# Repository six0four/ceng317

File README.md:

# I2C device addresses   
MAG3110 3-Axis Magnetometer (0x0E)   
Si4713 FM Transmitter with RDS (0x11)   
VCNL40x0 proximity sensor (0x13)   
LIS3DH 3-axis accelerometer (0x18)   
LSM303 Accelerometer & Magnetometer (0x19 for accelerometer and *0x1E for magnetometer)   
MCP9808 temp sensor (0x1A)   
MMA845x 3-axis Accelerometer (0x1C)   
LSM9DS0 9-axis IMU (0x1D for Accel/Mag, *0x6A for Gyro)   
*LSM303 Accelerometer & Magnetometer (0x19 for accelerometer and *0x1E for magnetometer)   
FXOS8700 Accelerometer/Magnetometer (0x1F)   
Chirp! Water sensor (0x20)   
FXAS21002 Gyroscope (0x21)   
MCP23008 I2C GPIO expander (0x22)   
MCP23017 I2C GPIO expander (0x23)   
VL53L0x ToF distance (0x24 software selectable)   
BNO055 IMU (0x28)   
TCS34725 color sensor (0x29)   
CAP1188 8-channel Capacitive Touch (0x2A)   
FT6x06 Capacitive Touch Driver (0x38)   
VEML6070 UV Index (0x39)   
SSD1305 monochrome OLED (0x3C)   
SSD1306 monochrome OLED (0x3D)   
HTU21D-F Humidity/Temp Sensor (0x40)   
STMPE610/STMPE811 Resistive Touch controller (0x41)   
HDC1008 Humidity/Temp sensor (0x42)   
ISL29125 Color Sensor (0x44)   
SHT31 Humidity/Temp sensor (0x45)   
TMP006 IR Temperature sensor (0x46)   
TMP007 IR Temperature sensor (0x47)   
YL-40 PCF8591 (0x48)   
TSL2561 light sensor (0x49)   
TMP102 Temperature sensor (0x4A)   
ADS1115 4-channel 16-bit ADC (0x4B)   
INA219 High-Side DC Current/Voltage sensor (0x4C)   
MB85RC I2C FRAM (0x50)   
Nintendo Nunchuck controller (0x52)   
ADXL345 3-axis accelerometer (0x53)   
MAX3010x Pulse & Oximetry sensor (0x57)   
TPA2016 I2C-controlled Amplifier (0x58)   
DRV2605 Haptic Motor Driver (0x5A)   
CCS811 VOC sensor (0x5B)   
AM2315 Humidity/Temp sensor (0x5C)   
MPR121 12-point capacitive touch sensor (0x5D)   
TEA5767 Radio receiver (0x60)   
Si5351A Clock Generator (0x61)   
MCP4725A1 12-bit DAC (0x62)   
MCP4725A2 12-bit DAC (0x64)   
MCP4725A3 12-bit DAC (0x66)   
DS3231 RTC (0x68)   
AMG8833 IR Thermal Camera Breakout (0x69)   
*LSM9DS0 9-axis IMU (0x1D for Accel/Mag, *0x6A for Gyro)   
L3GD20H gyroscope (0x6B)   
TCA9548 1-to-8 I2C Multiplexer (0x70)   
HT16K33 LED Matrix Driver (0x72)   
IS31FL3731 144-LED CharliePlex driver (0x74)   
PCA9685 16-channel PWM driver (0x75)   
MS5607/MS5611 Barometric Pressure (0x76)   
BME280 Temp/Barometric/Humidity (0x77)   
PN532 NFC/RFID reader (Use UART pins 8:TX and 10:RX)

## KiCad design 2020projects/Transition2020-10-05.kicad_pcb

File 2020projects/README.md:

# CENG 317
1. Two device power considerations:
    1. Second STM32 configured as an CAN rear: First is powered via Serial to TTL converter. As long as there is minimal load, joining the 3.3V pins would allow the second to also power from the Serial to TTL converter.
    2. Second STM32 configured as an STLink: Second is powered from USB using its regulator for 3.3V; it would also supply the first weakly over the 3.3V SWD pin.
    3. Second STM32 configured as an I2C slave: First is powered by USB using its regulator for 3.3V; ideally joining the 5V pins allows the second to also use its own regulator but for now as long as there is minimal load, joining the 3.3V pins would allow the second to also use the first's regulator.
2. Electronic part naming conventions:
    1. Resistors start with R followed by a number. R32 is a pull up that has yet to be placed.
	2. Capacitors start with a C followed by a number.
	3. Headers start with a J followed by a number.
	4. 3.3V net label used for CANmain/I2Cmaster/STLinkTarget STM32 (J0,J1).
	5. GND net label used for common connection to CANmain/I2Cmaster/STLinkTarget STM32 (J0,J1) and CANrear/I2Cslave/STLink STM32 (J2,J3). Although some designers use a ground disconnect and open drain design to separate circuits it is problematic when using shielded cables and considering what would happen when a cable gets pinched. We will try to disconnect power instead.
3. J Headers, note that uSD disconnect is simply removing the card:
    0. CANmain/I2Cmaster/STLinkTarget STM32
	1. CANmain/I2Cmaster/STLinkTarget STM32
	2. CANrear/I2Cslave/STLink STM32
	3. CANrear/I2Cslave/STLink STM32
	4. PCF8574, Joystick, 7 Segment disconnect
	5. Servo pin header
	6. Flash disconnect
	7. BME disconnect
	8. Flow control disconnect
	9. Flow control disconnect
	10. Programming port/for serial TTL cable
	11. Inter STM32 3.3V disconnect
	12. STLink voltage divider disconnect
	13. MOSIsd
	14. MISOsd
	15. SCKsd
	16. NSSsd
	17. MOSIflash
	18. MISOflash
	19. SCKflash
	20. NSSflash
	21. MOSIbme
	22. MISObme
	23. SCKbme
	24. NSSbme
	25. PCF8574 Interrupt disconnect
	26. PCF8574 SDA choice
	27. PCF8574 SCL choice
	28. CAN disconnect
	29. CAN disconnect
	30. CAN disconnect
	31. CAN LEDs power disconnect
	32. STLink header
	33. STLink R37 disconnect
	34. STLink NRST disconnect
	35. DS18B20 disconnect
	36. TTL3.3V disconnect
	37. SDAslave disconnect
	38. SCLslave disconnect
	39. LM75-OLED DC
	40. LM75-OLED RST
	41. OLED MOSI
	42. OLED SCK
	43. OLED NSS
	44. OLED 3.3V

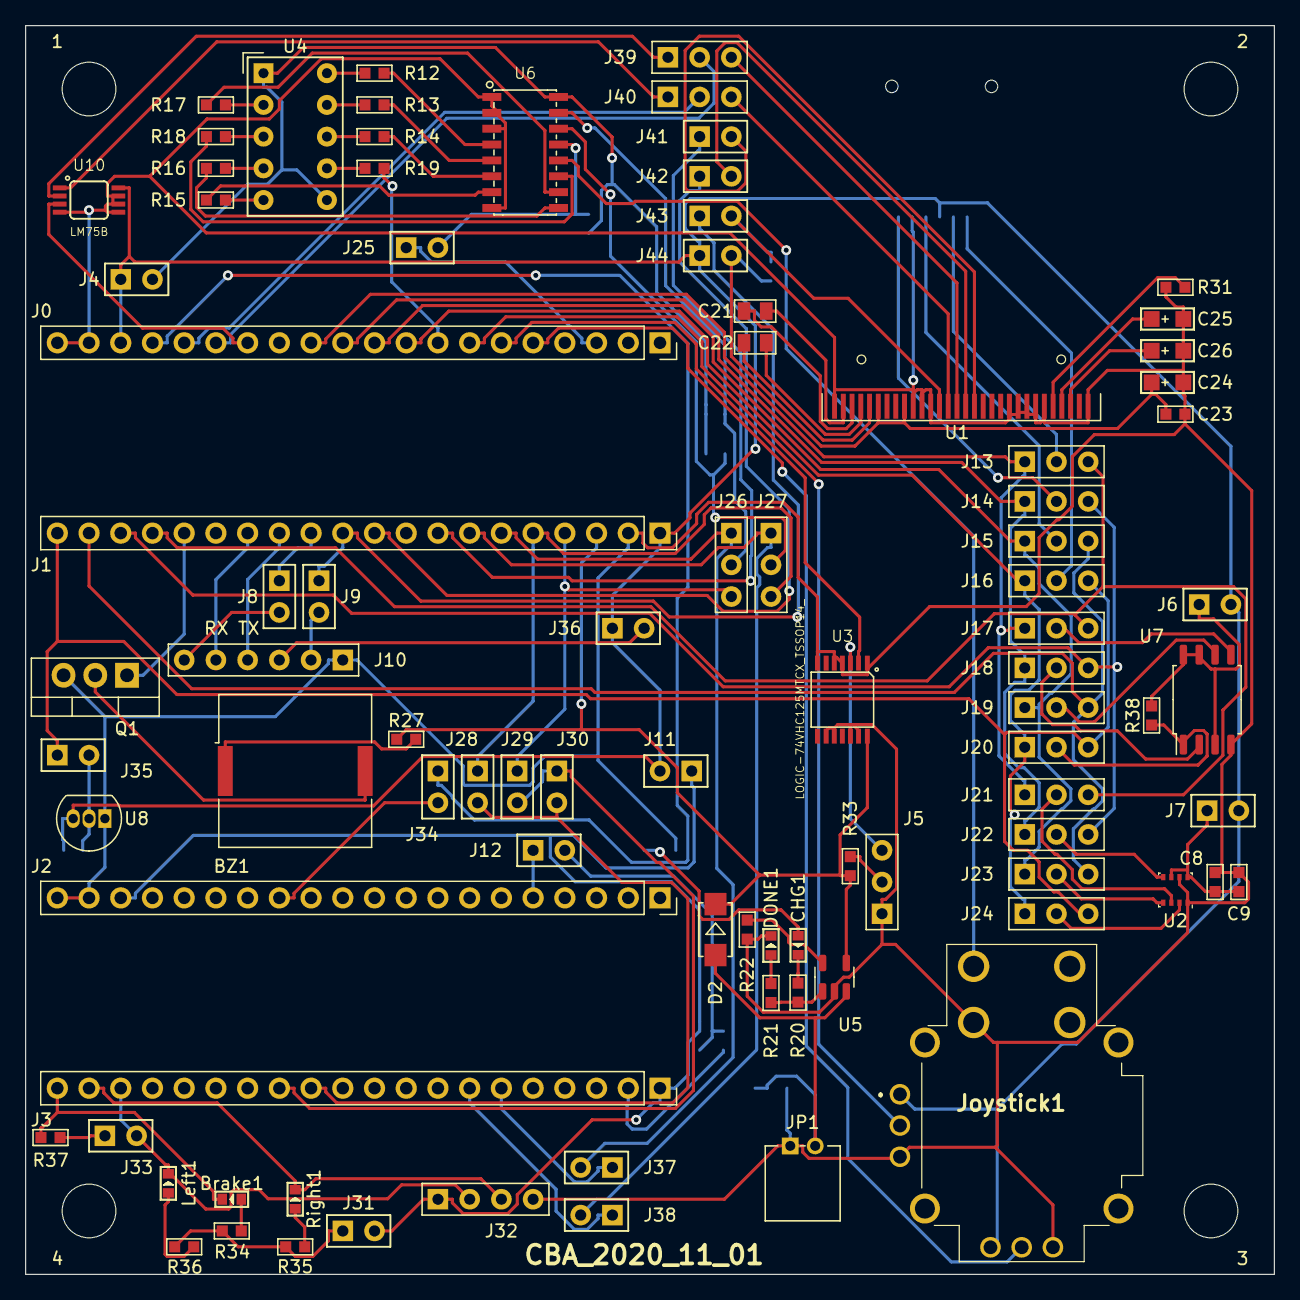
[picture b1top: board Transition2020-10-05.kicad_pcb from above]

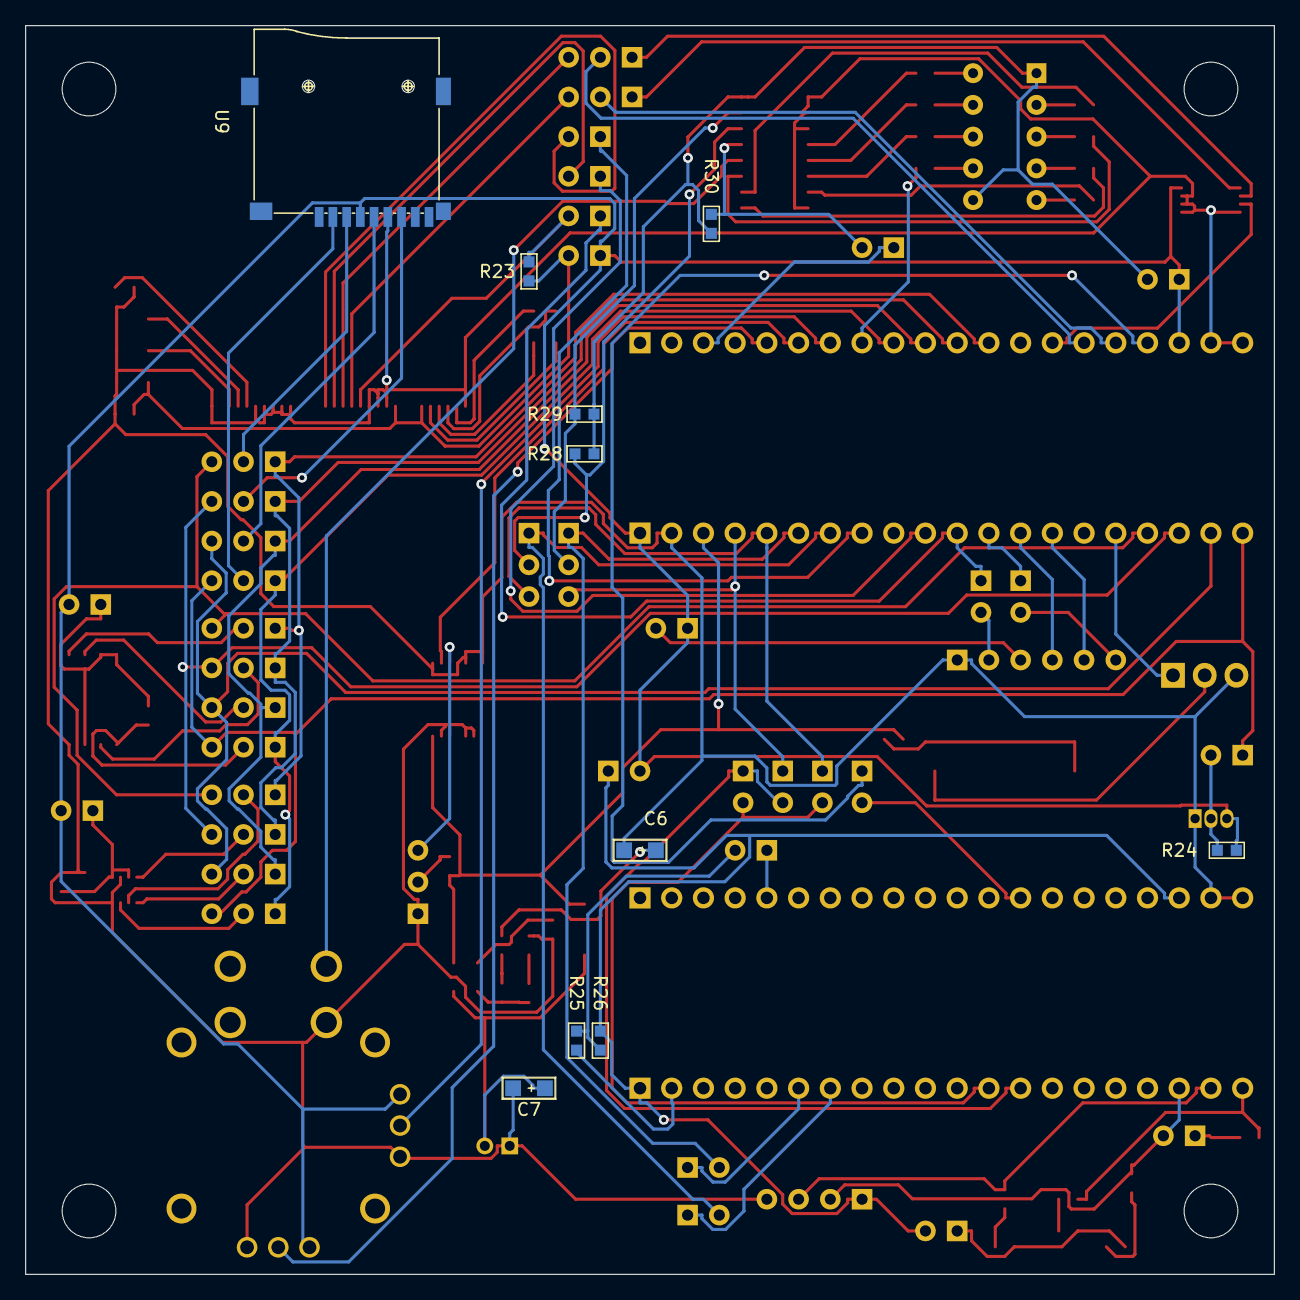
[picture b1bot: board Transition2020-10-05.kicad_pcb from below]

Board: 2 copper layers, 100.0 x 100.0 mm, 105 parts (10 on the bottom side), 111 nets.

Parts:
1, 2, 3, 4: MountingHole_4.3mm_M4_ISO7380
BZ1: Buzzer; Buzzer_Murata_PKLCS1212E
Brake1: LED-SMD-RED-DIFFUSED_0603_; LED-0603
C6, C7, C24, C25, C26: TANTALUM-SMD-10UF-10V-10%_AVX-A_; AVX-A(1206)
C8, C9, C23: CERAMIC-100NF-50V-10%-X7R_0603_; C0603
C21, C22: CERAMIC-2.2UF-25V-10%-X7R_0805_; C0805
CHG1: LED-SMD-RED-DIFFUSED_0603_; LED-0603
D2: SMD-DIODE-SCHOTTKY-40V-1A_DO-214AC_; DO-214AC
DONE1: SMD-LED-CLEAR-GREEN_0603_; LED-0603
J0, J1, J2, J3: Conn_01x20_Female; PinSocket_1x20_P2.54mm_Vertical
J4, J6, J7, J8, J9, J11, J12, J25, J28, J29, J30, J31, J33, J34, J35, J36, J37, J38, J41, J42, J43, J44: DIP-BLACK-MALE-HEADER-VERT_2P-2.54_; H2-2.54
J5, J13, J14, J15, J16, J17, J18, J19, J20, J21, J22, J23, J24, J26, J27, J39, J40: DIP-BLACK-MALE-HEADER-VERT_3P-2.54_; H3-2.54
J10: DIP-BLACK-MALE-HEADER_6P-2.54_; H6-2.54
J32: DIP-BLACK-MALE-HEADER-VERT_4P-2.54_; H4-2.54
JP1: DIP-JST-2P-2.0; H2-2.0-90D
Joystick1: RKJXK122400Y
Left1: SMD-LED-CLEAR-GREEN_0603_; LED-0603
Q1: MJE13005G; TO-220-3_Vertical
R12, R13, R14, R15, R16, R17, R18, R19, R34, R35, R36, R37: SMD-RES-220R-5%-1_10W_0603_; R0603
R20, R21, R27: SMD-RES-1K-5%-1_10W_0603_; R0603
R22, R38: SMD-RES-10K-5%-1_10W_0603_; R0603
R23, R24, R25, R26, R28, R29, R30: SMD-RES-4.7K-5%-1_10W_0603_; R0603
R31: SMD-RES-560K-5%-1_10W_0603_; R0603
R33: SMD-RES-10R-5%-1_10W_0603_; R0603
Right1: SMD-LED-CLEAR-GREEN_0603_; LED-0603
U1: OLED-128O064D
U2: BME280; Bosch_LGA-8_2.5x2.5mm_P0.65mm_ClockwisePinNumbering
U3: LOGIC-74VHC125MTCX_TSSOP14_; TSSOP14-0.65-5X4.4MM
U4: HDSP-7801
U5: MCP73831-2-OT; SOT-23-5
U6: PCF8574; SOP16-1.27-10.0X5.0MM
U7: W25Q32JVSS; SOIC-8_5.23x5.23mm_P1.27mm
U8: DS18B20; TO-92_Inline
U9: MICRO-SD-CARD-HOLDER-9P; MICRO-SD9+4P-SMD-16.1X14.5X1.85MM
U10: LM75B; MSOP8-0.65-3X3MM

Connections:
3.3V: J0.18, J1.1, J4.1, J6.2, J7.2, J11.2, J36.1, J44.1, Joystick1.1, Joystick1.4, R24.1, U8.3, U9.4, U10.8
3.3Vs: J2.18, J3.1, J11.1, J31.2, J32.1, R26.2
5V: D2.2, J1.3, R27.1, R33.1, U3.14, U5.4
GND: C6.2, C7.2, C8.2, C9.2, C23.2, C24.2, C25.2, C26.2, DONE1.2, J0.19, J0.20, J1.2, J2.19, J2.20, J5.1, J10.1, J32.4, JP1.1, Joystick1.3, Joystick1.6, Joystick1.C1, Q1.3, R22.1, R31.1, U1.1, U1.10, U1.11, U1.12, U1.21, U1.22, U1.23, U1.24, U1.25, U1.30, U2.1, U2.7, U3.1, U3.4, U3.5, U3.7, U3.9, U3.10, U3.12, U3.13, U5.2, U6.1, U6.2, U6.3, U6.8, U7.4, U8.1, U9.6, U10.4, U10.5, U10.6, U10.7
GNDs: J3.2, R25.1
MISO1: J0.11, J14.1, J18.1, J22.1
MISO2: J1.18, J14.3, J18.3, J22.3
MISObme: J22.2, U2.5
MISOflash: J18.2, U7.2
MISOsd: J14.2, U9.7
MOSI1: J0.12, J13.1, J17.1, J21.1
MOSI2: J1.17, J13.3, J17.3, J21.3
MOSIbme: J21.2, U2.3
MOSIflash: J17.2, U7.5
MOSIsd: J13.2, U9.3
NRST: J0.17, J34.1
NSS1: J0.9, J16.1, J20.1, J24.1
NSS2: J1.20, J16.3, J20.3, J24.3, J35.1
NSSbme: J24.2, U2.2
NSSflash: J20.2, R38.1, U7.1
NSSsd: J16.2, U9.2
unnamed: BZ1.1, R27.2
unnamed: BZ1.2, Q1.2
unnamed: Brake1.1, R34.2
unnamed: C6.1, CHG1.1
unnamed: C7.1, D2.1, JP1.2, U5.3
unnamed: C8.1, C9.1, J7.1, U2.6, U2.8
unnamed: C21.1, U1.3
unnamed: C21.2, U1.2
unnamed: C22.1, U1.5
unnamed: C22.2, U1.4
unnamed: C23.1, C24.1, J44.2, R23.2, U1.6, U1.9
unnamed: C25.1, U1.27
unnamed: C26.1, U1.28
unnamed: CHG1.2, R20.2
unnamed: DONE1.1, R21.2
unnamed: J4.2, R28.2, R29.2, R30.2, U4.1, U4.6, U6.16
unnamed: J5.2, R33.2
unnamed: J5.3, U3.3
unnamed: J6.1, R38.2, U7.3, U7.7, U7.8
unnamed: J9.2, J10.2
unnamed: J10.3, J36.2
unnamed: J8.2, J10.6
unnamed: J12.2, R25.2, R26.1
unnamed: J25.2, R30.1, U6.13
unnamed: J26.2, R29.1, U6.15
unnamed: J27.2, R28.1, U6.14
unnamed: J31.1, R34.1, R35.1, R36.1
unnamed: J33.1, R37.2
unnamed: J35.2, R24.2, U8.2
unnamed: J39.1, U10.2
unnamed: J39.3, U1.15
unnamed: J40.1, U10.1
unnamed: J40.3, U1.14
unnamed: J41.2, U1.17
unnamed: J42.2, U1.16
unnamed: J43.2, R23.1, U1.13
unnamed: Left1.1, R36.2
unnamed: R12.1, U6.4
unnamed: R12.2, U4.10
unnamed: R13.1, U6.5
unnamed: R13.2, U4.9
unnamed: R14.1, U6.6
unnamed: R14.2, U4.8
unnamed: R15.1, U6.7
unnamed: R15.2, U4.5
unnamed: R16.1, U6.9
unnamed: R16.2, U4.4
unnamed: R17.1, U6.10
unnamed: R17.2, U4.2
unnamed: R18.1, U6.11
unnamed: R18.2, U4.3
unnamed: R19.2, U4.7
unnamed: R20.1, R21.1, U5.1
unnamed: R22.2, U5.5
unnamed: R31.2, U1.26
unnamed: R35.2, Right1.1
PA0: J0.5, Joystick1.5
PA0s: J2.5, J12.1
PA1: J0.6, U3.2
PA2: J0.7, Joystick1.2
PA3: J0.8, R19.1
PA5: J0.10, J15.1, J19.1, J23.1
PA8: J1.16, Q1.1
PA10: J1.14, J10.5
PA11: J1.13, J10.4
PA11s: J3.13, J29.2, J30.1
PA12: J1.12, J8.1
PA12s: J3.12, J28.2, J30.2
PA15: J1.11, J9.1, J43.1
PB0s: J2.13, J34.2
PB1: J0.14, U10.3
PB3: J1.10, J42.1
PB5: J1.8, J41.1
PB6: J1.7, J27.1, J38.2
PB6s: J3.7, J38.1
PB7: J1.6, J26.1, J37.2
PB7s: J3.6, J37.1
PB8: J1.5, J27.3, J28.1
PB9: J1.4, J26.3, J29.1
PB10: J0.15, J39.2
PB11: J0.16, J40.2
PB12s: Brake1.2, J3.20, R37.1
PB13: J1.19, J15.3, J19.3, J23.3
PB13s: J3.19, J32.3, Right1.2
PB14s: J3.18, J32.2, J33.2, Left1.2
PC14: J0.3, J25.1
SCKbme: J23.2, U2.4
SCKflash: J19.2, U7.6
SCKsd: J15.2, U9.5
SEL+: Joystick1.D1, U6.12

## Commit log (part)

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2018-09-12 Starting to update weekly entries to match critical path
2018-09-13 Rubrics moved to ceng 317
2018-09-13 Wk02 update
2018-09-17 Added repository links
2018-09-17 Removed link from last year
2018-09-17 Links tested
2018-09-18 Updated links
2018-09-18 link corrected
2018-09-18 groups formed
2018-09-18 groups continue to be formed
2018-09-18 Rubric link fixed for wk04
2018-09-18 updating links
2018-09-18 Added link names
2018-09-18 Links corrected
2018-09-18 Address 0x42
2018-09-18 Added a link
2018-09-18 Updated schedule
2018-09-25 Links updated
2018-09-25 Updated link
2018-09-25 typo fixed
2018-09-25 Added link
2018-09-25 Address change
2018-09-25 Group change
2018-09-25 Address chosen
2018-09-26 Group creation
2018-09-27 Update to align with Fall 2018 critical path
2018-09-27 formatting update
2018-09-27 Improved text
2018-09-27 date solidified
2018-09-27 example added
2018-10-02 vm directions
2018-10-02 updates hang
2018-10-06 Capitalization?
2018-10-16 Update for soldering
2018-10-16 Marko repo change
2018-10-16 Repo name change
2018-10-16 Move from gitlab
2018-10-30 Added 6 pin image
2018-10-30 Updated to include part image
2018-10-30 Socket part number added
2018-10-30 Pins added
2018-10-30 Kelly's better part
2018-10-31 Vlad update
2018-11-03 Clarification update
2018-11-06 Week 10 blog entry
2018-11-06 missing double quote added
2018-11-06 Fixed spelling error
2018-11-20 Presentation schedule added
2018-11-20 Updated 4th slide to things you should already have
2018-11-22 Updated project names
2018-11-27 Added columns
2018-11-27 Column heading fix
2019-01-17 link update
2019-01-24 Specific turned generic
2019-08-28 folder name change
2019-08-28 Fall 2019 update
2019-08-28 Heading size test
2019-08-28 Extended heading test
2019-08-28 Headings homogenized
2019-08-28 Updated menu
2019-09-02 Week 1 update
2019-09-02 Riipen links added
2019-09-02 fixing links
2019-09-02 Cleaning up link text
2019-09-02 Added keyword
2019-09-03 Duplicate entries removed
2019-09-03 Added real files
2019-09-03 Aligned with critical path
2019-09-03 Updating proposal form
2019-09-03 Added more detail
2019-09-05 Fixed typo
2019-09-10 14 week term
2019-09-12 Added project links
2019-09-12 Three more project links
2019-09-12 List correction
2019-09-12 Added part of a url
2019-09-16 Groups added
2019-09-16 Project links added
2019-09-16 Shifting last year's projects
2019-09-16 Typo alignment
2019-09-16 Updated project order
2019-09-18 Updated sensor/effector choices
2019-09-19 Updated project list
2019-09-19 Updated project link
2019-09-19 Part numbers added
2019-09-19 Updated Part Numbers
2019-09-19 Added details
2019-09-19 Updated devices
2019-09-20 Added sensor
2019-09-24 Updated sensor choices
2019-09-24 Sensor change
2019-09-25 Updated details/order/format
2019-09-26 Week 4 updates
2019-09-27 Updated choices
2019-10-01 wk5 update
2019-10-01 Updated platform
2019-10-07 Reminder to work on OS/Bootloader
2019-10-07 Header/socket part numbers
2019-10-11 Updated for 2019
2019-11-19 Added right angle socket
2020-04-07 Laser example update
2020-09-06 2020 update
2020-09-07 example
2020-09-07 Adding details
2020-09-08 Adding links
2020-09-09 Addition
2020-09-15 Added S1
2020-09-17 Add document
2020-09-17 Considering pins
2020-09-17 Pin updates
2020-09-17 Added GND
2020-09-29 Mistake in naming
2020-09-29 Naming mistake
2020-10-14 First order
2020-11-03 CBA_2020_11_01
2020-11-03 mechanical
2020-11-03 LaserFiles
2020-11-03 Shifted to match PCB X coordinate
2020-11-03 Revert mistake
2020-11-05 Added STM32 on Guide layer
2020-11-05 Guide layer non-printing
2020-11-05 Added 2 cm
2020-11-05 Tolerance added to servo mount
2020-11-17 Transition to KiCad
